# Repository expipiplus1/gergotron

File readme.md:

#

## Pins:

### PS/2:

TXB0104: http://www.ti.com/lit/ds/symlink/txb0104.pdf

| PS/2     | TXB0104   | P3 | Arduino | DE10-nano | Notes           |
|----------|-----------|----|---------|-----------|-----------------|
| J1 clock | channel 1 | 5  | IO13    | AH12      |                 |
| J1 data  | channel 2 | 2  | SDA     | AH9       |                 |
| J2 clock | channel 3 | 7  | IO11    | AG16      |                 |
| J2 data  | channel 4 | 6  | IO12    | AH11      |                 |
|          | OE        | 1  | SCL     | AG11      | 4.7kΩ pull-down |

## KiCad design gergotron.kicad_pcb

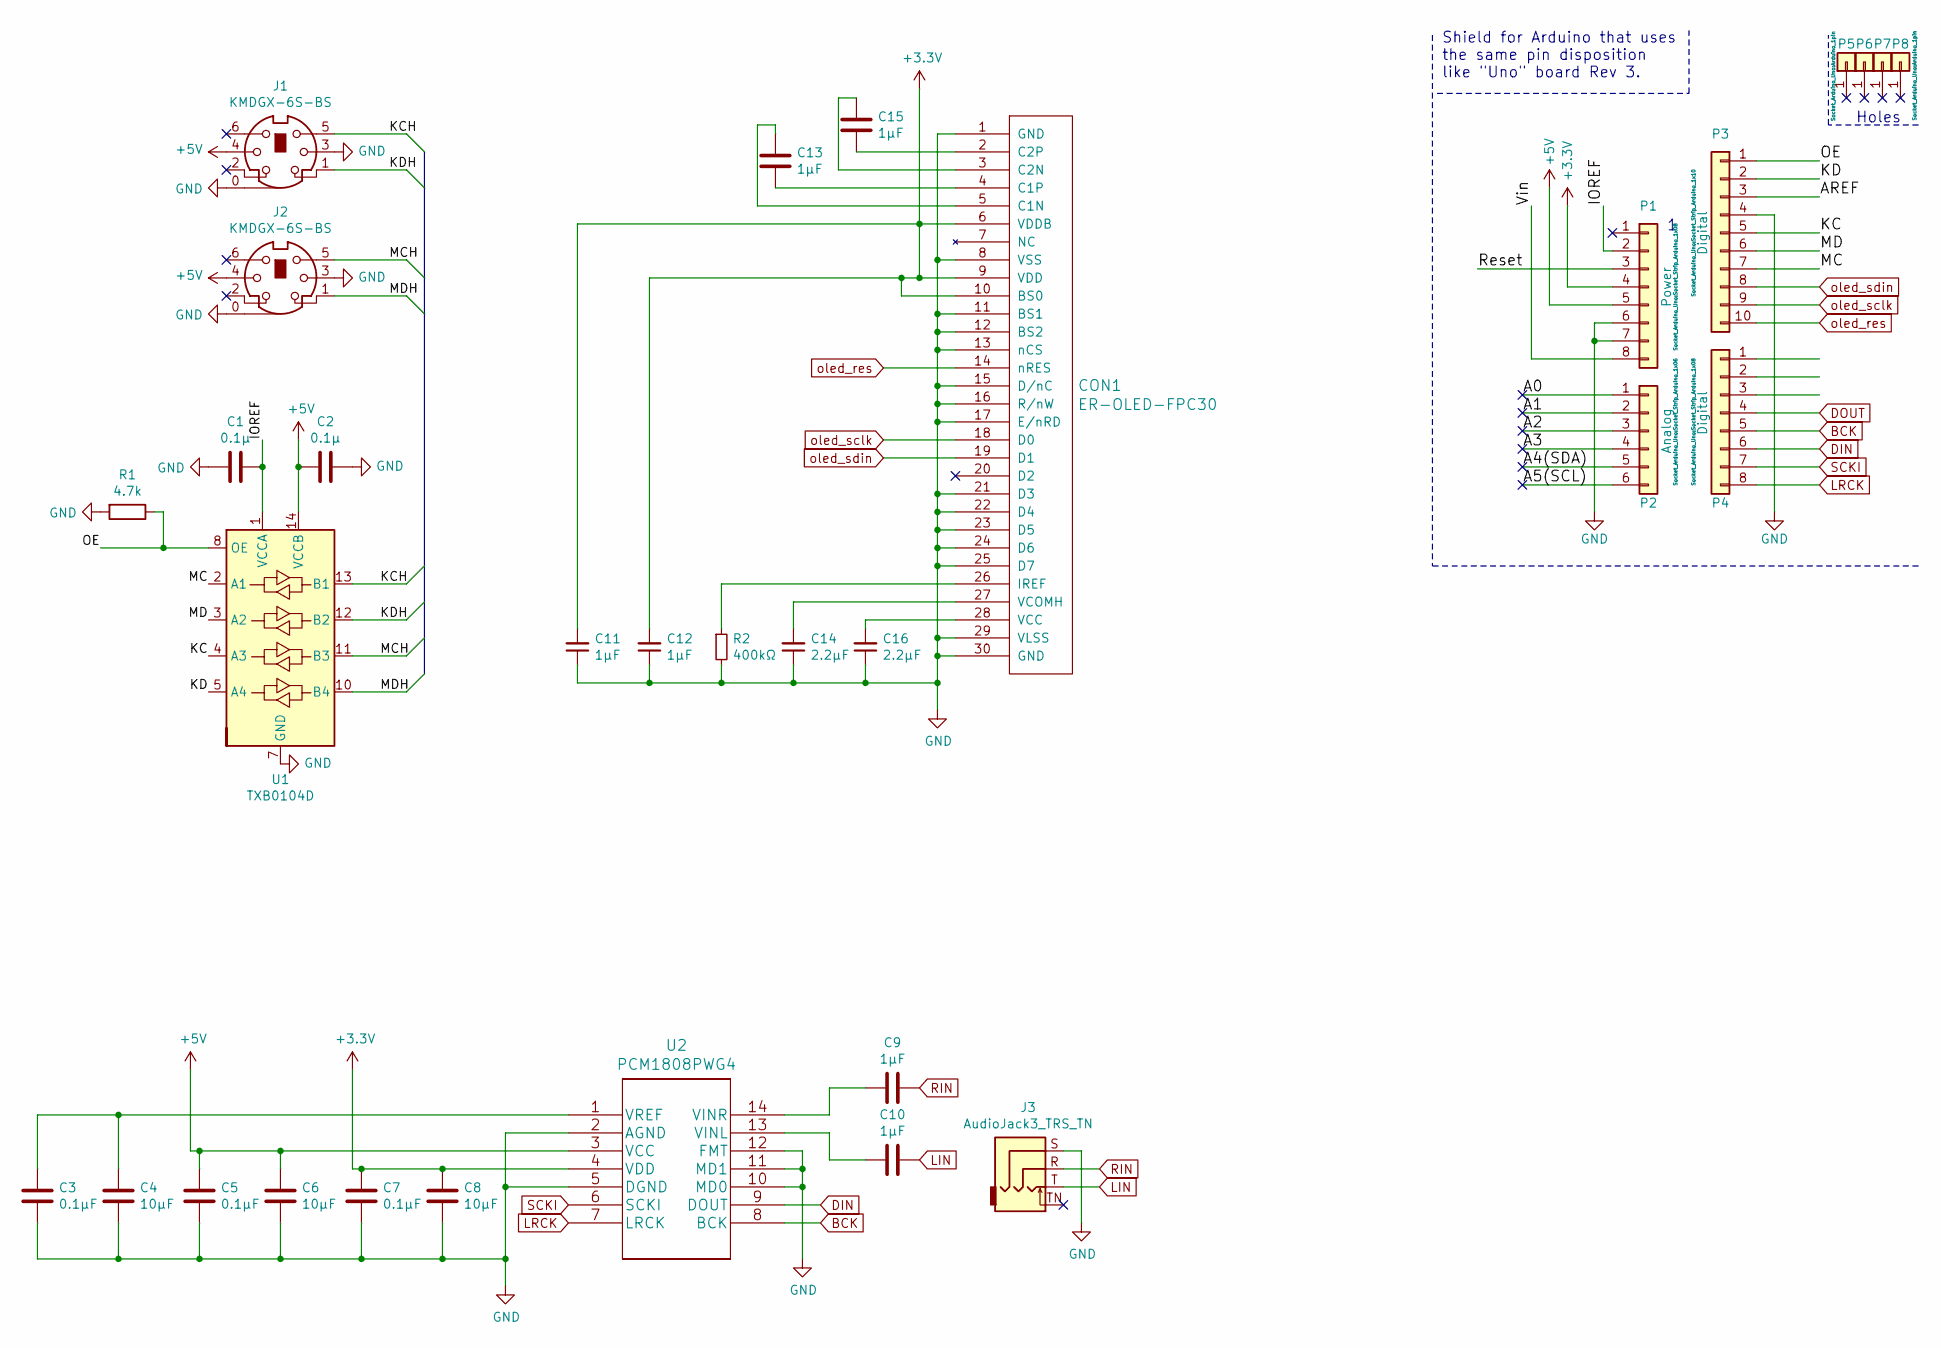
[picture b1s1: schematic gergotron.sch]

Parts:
C1, C2: 0.1μ; C_0603_1608Metric
C3, C5, C7: 0.1μF; C_0603_1608Metric
C4, C6, C8: 10μF; C_0805_2012Metric
C9, C10, C11, C12, C13, C15: 1μF; C_0603_1608Metric
C14, C16: 2.2μF; C_0603_1608Metric
CON1: ER-OLED-FPC30; er-oled-fpc30-flipped
J1, J2: KMDGX-6S-BS; kmdgx-6s-bs
J3: AudioJack3_TRS_TN; sj-352x-smt
P1: Power; Socket_Strip_Arduino_1x08
P2: Analog; Socket_Strip_Arduino_1x06
P3: Digital; Socket_Strip_Arduino_1x10
P4: Digital; Socket_Strip_Arduino_1x08
P5, P6, P7, P8: CONN_01X01; Arduino_1pin
R1: 4.7k; R_0603_1608Metric
R2: 400kΩ; R_0603_1608Metric
U1: TXB0104D; SOIC-14_3.9x8.7mm_P1.27mm
U2: PCM1808PWG4

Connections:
+3V3: C7.1, C8.1, C11.2, C12.2, CON1.6 (VDDB), CON1.9 (VDD), CON1.10 (BS0), P1.4, U2.4 (VDD)
+5V: C2.1, C5.1, C6.1, J1.4, J2.4, P1.5, U1.14 (VCCB), U2.3 (VCC)
/A0: P2.1
/A1: P2.2
/A2: P2.3
/A3: P2.4
/A4(SDA): P2.5
/A5(SCL): P2.6
/AREF: P3.3
/IOREF: C1.2, P1.2, U1.1 (VCCA)
/KC: P3.5, U1.4 (A3)
/KCH: J1.5, U1.13 (B1)
/KD: P3.2, U1.5 (A4)
/KDH: J1.1, U1.12 (B2)
/MC: P3.7, U1.2 (A1)
/MCH: J2.5, U1.11 (B3)
/MD: P3.6, U1.3 (A2)
/MDH: J2.1, U1.10 (B4)
/OE: P3.1, R1.1, U1.8 (OE)
/Reset: P1.3
/Vin: P1.8
BCK: P4.5, U2.8 (BCK)
DIN: P4.6, U2.9 (DOUT)
DOUT: P4.4
GND: C1.1, C2.2, C3.2, C4.2, C5.2, C6.2, C7.2, C8.2, C11.1, C12.1, C14.1, C16.1, CON1.1 (GND), CON1.8 (VSS), CON1.11 (BS1), CON1.12 (BS2), CON1.13 (nCS), CON1.15 (D/nC), CON1.16 (R/nW), CON1.17 (E/nRD), CON1.21 (D3), CON1.22 (D4), CON1.23 (D5), CON1.24 (D6), CON1.25 (D7), CON1.29 (VLSS), CON1.30 (GND), J1.0, J1.3, J2.0, J2.3, J3.S, P1.6, P1.7, P3.4, R1.2, R2.2, U1.7 (GND), U2.2 (AGND), U2.5 (DGND), U2.10 (MD0), U2.11 (MD1), U2.12 (FMT)
LIN: C10.2, J3.T
LRCK: P4.8, U2.7 (LRCK)
unnamed: C3.1, C4.1, U2.1 (VREF)
unnamed: C9.1, U2.14 (VINR)
unnamed: C10.1, U2.13 (VINL)
unnamed: C13.1, CON1.5 (C1N)
unnamed: C13.2, CON1.4 (C1P)
unnamed: C14.2, CON1.27 (VCOMH)
unnamed: C15.1, CON1.3 (C2N)
unnamed: C15.2, CON1.2 (C2P)
unnamed: C16.2, CON1.28 (VCC)
unnamed: CON1.26 (IREF), R2.1
RIN: C9.2, J3.R
SCKI: P4.7, U2.6 (SCKI)
oled_res: CON1.14 (nRES), P3.10
oled_sclk: CON1.18 (D0), P3.9
oled_sdin: CON1.19 (D1), P3.8

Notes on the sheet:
Holes
Shield for Arduino that uses the same pin disposition like "Uno" board Rev 3.

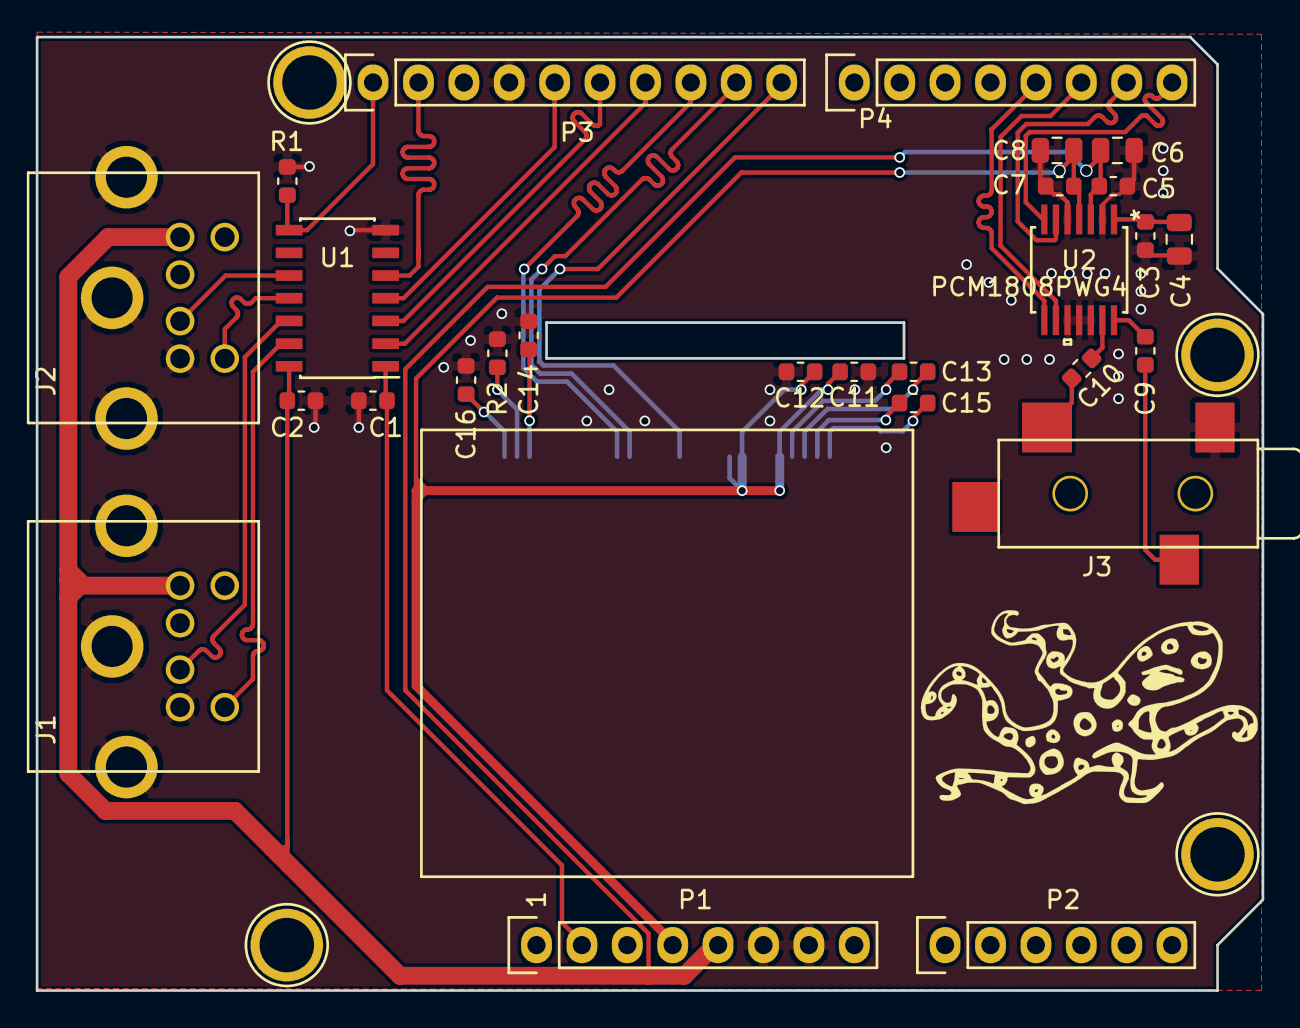
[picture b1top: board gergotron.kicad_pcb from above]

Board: 2 copper layers, 68.6 x 53.3 mm, 32 parts (1 on the bottom side), 32 nets.

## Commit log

2018-11-15 initial commit, template project
2018-11-15 ps/2 done
2018-11-15 Add audio in
2018-11-17 Add oled display
2018-11-17 power to the oled
2018-11-17 add gitignore
2018-11-18 Add lib table
2018-11-19 Fiddle traces
2018-11-19 Tidy up schematic and connect unused data wires to gnd
2018-11-19 Start work on the DAC
2019-01-12 remove audio out
2019-01-14 Added octopus
2019-03-08 Octo on pcb
2019-03-08 Readme with ps/2 pins

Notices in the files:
parts and their libraries:
Copyright 2016 Accelerated Designs. All rights reserved.
